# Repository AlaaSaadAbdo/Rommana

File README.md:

# Rommana
A 30 key well powered by Xiao BLE

### Parts
- MCU: 2x Seeeduino Xiao BLE
- On/Off Switch: 2x SS12 °F15 3 Pin On/On Mini Slide Switch
- Reset button: 2x 2 Pin DIP 6 x 6 x 5
- 30 MX switches
- Optional:
  - Ameoba PCBS
  - MX Hotswap sockets

## Pictures

## Build logs
- A hand wire by Rafael Romao: [Build Log](https://github.com/rafaelromao/keyboards/blob/main/docs/rommana.md)
- Build log with MCU holder by Oliver Säfström: [Build Log](https://github.com/safstromo/keyboards/blob/main/buildlogs/rommana/rommana.md)

## Credits and references
- This keyboard wouldn't be possible without the help and videos of [Quentin](https://github.com/bstiq) of [BastardKB](https://bastardkb.com)
- Fix the MCU holder power circuit:
  -  [safstromo](https://github.com/safstromo)
  -  [il](https://github.com/il2076)

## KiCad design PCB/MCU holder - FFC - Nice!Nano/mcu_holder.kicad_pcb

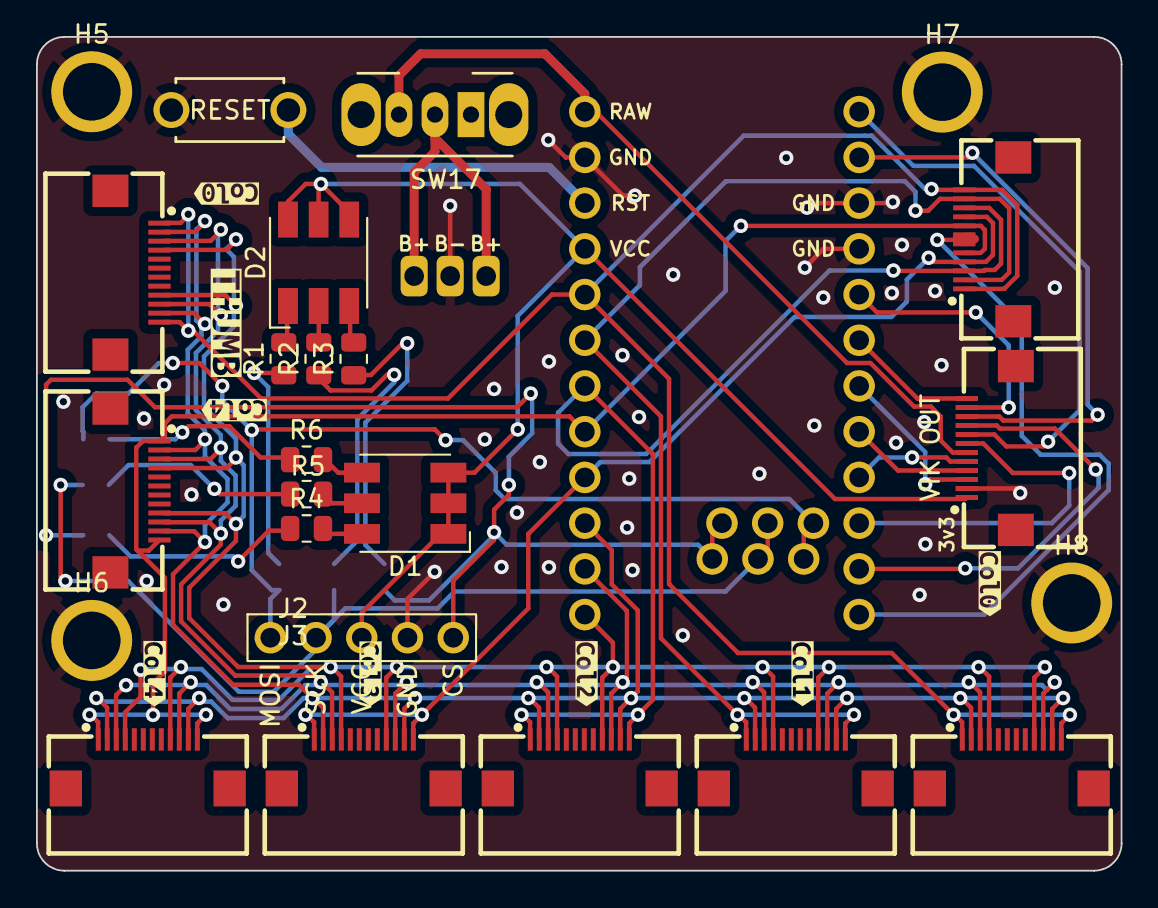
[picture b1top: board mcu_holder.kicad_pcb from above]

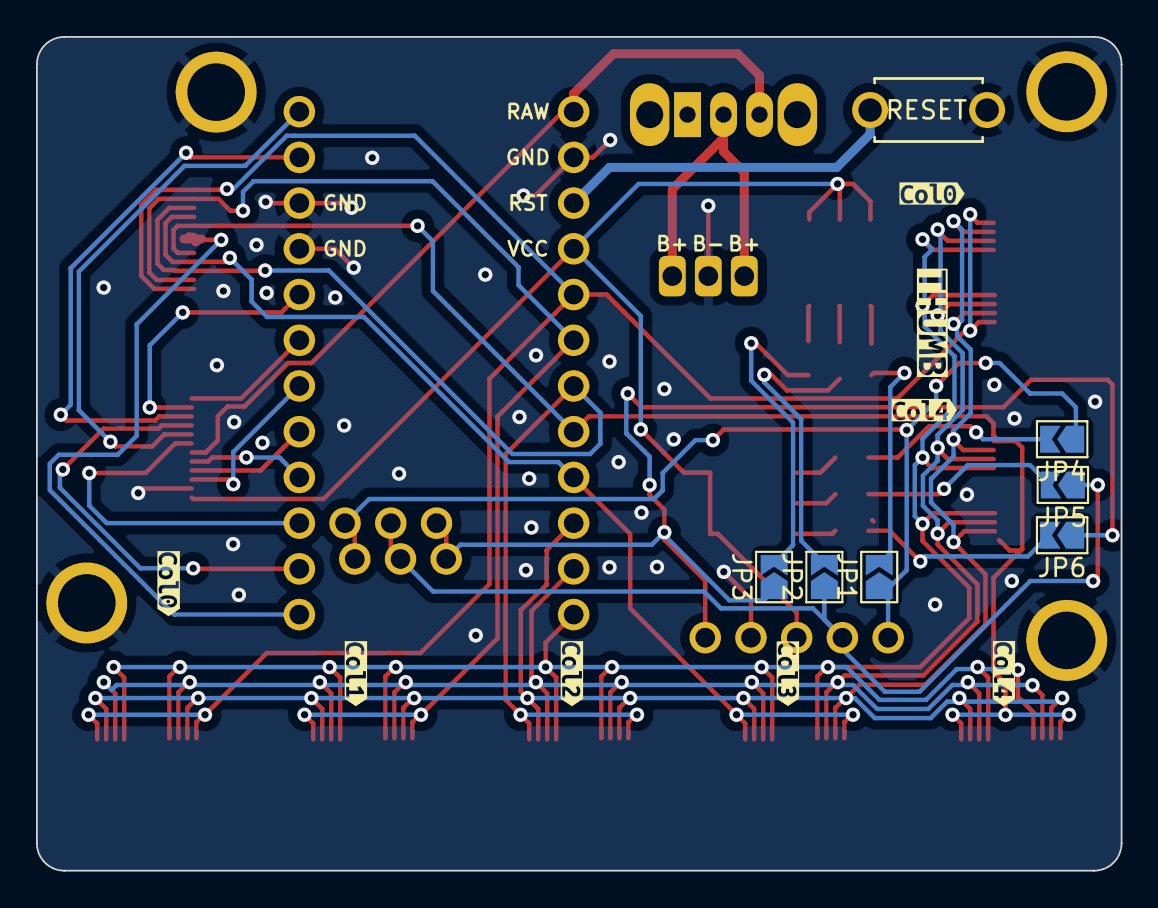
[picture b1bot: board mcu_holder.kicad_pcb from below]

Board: 2 copper layers, 60.3 x 46.3 mm, 48 parts (15 on the bottom side), 38 nets.

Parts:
D1: SMLVN6RGB; MHP5050RGBDT
D2: SMLVN6RGB; LED_RGB_5050-6
Display1: nice!view; nice_view
H5, H6, H7, H8: MountingHole_Pad; MountingHole_M3
J1: N!N; MCU_nice-nano
J2, J11, J12, J13, J14, J15, J16, J17: Conn_01x12_Socket; FPC-SMD_FPC05012-09200-.5mm-rev
J3: vik-keyboard-connector-horizontal
J7: Conn_01x08_Female; 3JST_BAT
JP1, JP2, JP3, JP4, JP5, JP6: Jumper_2_Open; SolderJumper-2_P1.3mm_Open_TrianglePad1.0x1.5mm
R1, R4: 47; R_0805_2012Metric
R2, R5: 180; R_0805_2012Metric
R3, R6: 390; R_0805_2012Metric
SW16: SW_Push; ResetSW
SW17: SW_SPDT; SW_CuK_OS102011MA1QN1_SPDT_Angled
kibuzzard-6399CB9D, kibuzzard-6399CB9D#2, kibuzzard-6399CB9D#3, kibuzzard-6399CB9D#4: G***; kibuzzard-6399CB9D
kibuzzard-6399CBBA, kibuzzard-6399CBBA#2: G***; kibuzzard-6399CBBA
kibuzzard-6399CBC9, kibuzzard-6399CBC9#2: G***; kibuzzard-6399CBC9
kibuzzard-6399CBD2, kibuzzard-6399CBD2#2: G***; kibuzzard-6399CBD2
kibuzzard-6399CBDB, kibuzzard-6399CBDB#2, kibuzzard-6399CBDB#3, kibuzzard-6399CBDB#4: G***; kibuzzard-6399CBDB
kibuzzard-6399CC4D, kibuzzard-6399CC4D#2: G***; kibuzzard-6399CC4D

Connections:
+3V3: D1.2 (BA), D1.4 (RA), D1.6 (GA), D2.1 (BK), D2.3 (RK), D2.5 (GK), Display1.3 (VCC), J1.21 (3V3), J3.1 (3V3)
B: JP1.2 (B), R1.1
B2: JP4.2 (B), R6.1
BAT+: J7.1, J7.3, SW17.2 (B)
BATT_OR_5V: J1.24 (BAT), J3.6 (5V), SW17.3 (C)
G: JP2.2 (B), R2.1
G2: JP5.2 (B), R5.1
GND: Display1.4 (GND), H5.1, H6.1, H7.1, H8.1, J1.3 (GND), J1.4 (GND), J1.23 (GND), J3.2 (GND), J7.2, SW16.2
GPIO_AD1: J1.10 (011), J3.7 (GPIO_AD1)
GPIO_AD2: J1.11 (104), J3.9 (GPIO_AD2)
MISO: J1.5 (017), J3.11 (MISO)
MOSI: J1.1 (006), J3.8 (MOSI)
NVCS: Display1.5 (CS), J1.33 (107), JP3.1 (A), JP6.1 (A)
NVMOSI: Display1.1 (MOSI), J1.31 (101), JP1.1 (A), JP4.1 (A)
NVSCK: Display1.2 (SCK), J1.32 (102), JP2.1 (A), JP5.1 (A)
unnamed: D1.1 (BK), R4.2
unnamed: D1.5 (GK), R6.2
unnamed: D1.3 (RK), R5.2
unnamed: D2.2 (BA), R1.2
unnamed: D2.6 (GA), R3.2
unnamed: D2.4 (RA), R2.2
R: JP3.2 (B), R3.1
R2: JP6.2 (B), R4.1
RESET: J1.22 (RST), SW16.1
RGB_LED_OUT: J1.9 (100), J3.5 (RGB_LED_OUT)
SCL: J1.8 (024), J3.4 (SCL)
SCLK: J1.6 (020), J3.12 (SCLK)
SDA: J1.7 (022), J3.3 (SDA)
SPI_CS: J1.2 (008), J3.10 (SPI_CS)
col0: J1.20 (031), J2.1, J2.12, J15.1, J15.12, J16.1, J16.12
col1: J1.19 (029), J2.2, J2.11, J11.1, J11.12
col2: J1.18 (002), J2.3, J2.10, J12.1, J12.12
col3: J1.16 (113), J2.4, J2.9, J13.1, J13.12
col4: J1.17 (115), J2.5, J2.8, J14.1, J14.12, J17.1, J17.12
row_0: J1.15 (111), J11.2, J11.11, J12.2, J12.11, J13.2, J13.11, J14.2, J14.11, J15.2, J15.11, J16.2, J16.11, J17.2, J17.11
row_1: J1.14 (010), J11.3, J11.10, J12.3, J12.10, J13.3, J13.10, J14.3, J14.10, J15.3, J15.10, J16.3, J16.10, J17.3, J17.10
row_2: J1.13 (009), J11.4, J11.9, J12.4, J12.9, J13.4, J13.9, J14.4, J14.9, J15.4, J15.9, J16.4, J16.9, J17.4, J17.9
row_3: J1.12 (106), J2.6, J2.7

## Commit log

2022-09-12 Rommana
2022-09-15 Improve middle/ring/pinky position
2022-09-17 add tented version
2022-09-17 doc: add optional parts
2022-12-04 improved column support in 15 degree tented
2022-12-07 add credits
2022-12-28 flex pcb and body for for it
2023-03-26 add Rafael's Build log
2024-04-17 fix mcu holder power circuit
2024-04-17 credits for MCU power circuit fix
2024-05-21 Add License
2024-09-04 Spelling correction
2025-06-23 Rommana FFC version
